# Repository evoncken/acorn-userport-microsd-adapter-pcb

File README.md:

Cheap MicroSD adapter for MMFS on Acorn BBC Micro
=================================================

There are several modern options to replace aging cassette tape or floppy
disc storage on your Acorn BBC (Master) micro.

MicroSD cards are very popular. You can wire up a 5V compatible
(important!) MicroSD board from Adafruit (ada-254) or use a generic
Arduino MicroSD board.

This repository contains the KiCad schematic, PCB layout as well as the
Gerber files for a simple "MicroSD board to Acorn userport" adapter.

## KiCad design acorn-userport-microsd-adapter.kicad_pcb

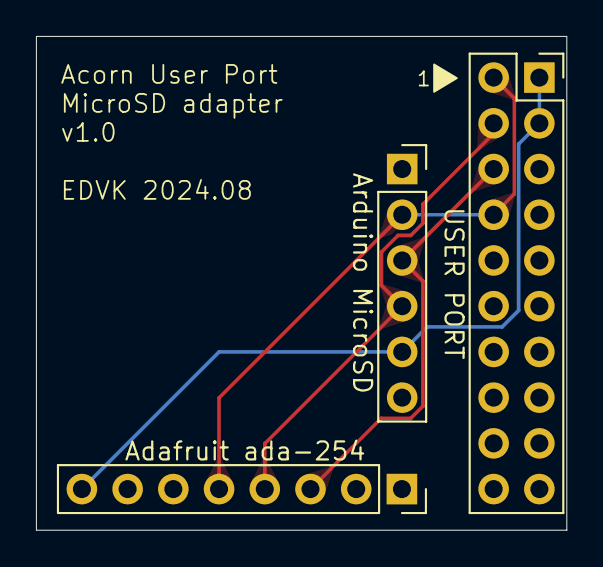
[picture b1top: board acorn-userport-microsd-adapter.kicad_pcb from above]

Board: 2 copper layers, 29.5 x 27.4 mm, 3 parts (0 on the bottom side), 5 nets.

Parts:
J1: Arduino MicroSD Adapter; PinSocket_1x06_P2.54mm_Vertical
J3: Adafruit (ada-254); PinSocket_1x08_P2.54mm_Vertical
UserPort1: IDC 2x10; PinSocket_2x10_P2.54mm_Vertical

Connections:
/MISO: J1.4, J3.4, UserPort1.4
/MOSI: J1.3, J3.3, UserPort1.6
/SCK: J1.2, J3.5, UserPort1.2, UserPort1.8
GND: J1.1, J1.6, J3.2, J3.6, UserPort1.5, UserPort1.7, UserPort1.9, UserPort1.11, UserPort1.13, UserPort1.15, UserPort1.17, UserPort1.19
VCC: J1.5, J3.8, UserPort1.1, UserPort1.3

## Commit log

2024-08-25 Cheap MicroSD adapter for MMFS on Acorn BBC Micro
    KiCad design for an adapter PCB that connects Adafruit ada-254
    or generic Arduino 5V MicroSD boards to an Acorn BBC Micro user port.
